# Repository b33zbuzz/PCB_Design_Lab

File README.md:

# PCB_Design_Lab

PCB_Design_Lab is a repository containing resources, designs, and documentation for printed circuit board (PCB) design and experimentation. This repository is intended to provide reference designs, tutorials, and simulation files for students and professionals involved in PCB design projects.

## Features
- Example PCB designs for specific applications.
- Tutorials on PCB design tools and workflows.
- Documentation for each design.

## File Structure
```
PCB_Design_Lab/
├── first/
│   ├── first-backups/            # Backup files for the project
│   │   ├── first-2024-04-02_143817.zip   # Backup from 2024-04-02
│   │   ├── first-2024-04-02_145749.zip   # Backup from 2024-04-02
│   │   ├── first-2024-04-03_172012.zip   # Backup from 2024-04-03
│   │   ├── first-2024-04-09_163603.zip   # Backup from 2024-04-09
│   │   ├── first-2024-04-09_164715.zip   # Backup from 2024-04-09
│   │   ├── first-2024-04-09_170915.zip   # Backup from 2024-04-09
│   │   ├── first-2024-04-09_174335.zip   # Backup from 2024-04-09
│   │   ├── first-2024-04-09_175404.zip   # Backup from 2024-04-09
│   │   ├── first-2024-04-15_153141.zip   # Backup from 2024-04-15
│   │   ├── first-2024-04-15_154005.zip   # Backup from 2024-04-15
│   │   ├── first-2024-04-16_141746.zip   # Backup from 2024-04-16
│   │   ├── first-2024-04-20_152721.zip   # Backup from 2024-04-20
│   │   ├── first-2024-04-20_153831.zip   # Backup from 2024-04-20
│   │   ├── first-2024-04-20_154842.zip   # Backup from 2024-04-20
│   │   ├── first-2024-04-20_155845.zip   # Backup from 2024-04-20
│   │   ├── first-2024-04-20_161707.zip   # Backup from 2024-04-20
│   │   ├── first-2024-04-21_213943.zip   # Backup from 2024-04-21
│   │   ├── first-2024-04-21_214944.zip   # Backup from 2024-04-21
│   │   ├── first-2024-04-21_223350.zip   # Backup from 2024-04-21
│   │   ├── first-2024-04-21_224453.zip   # Backup from 2024-04-21
│   │   ├── first-2024-04-21_233836.zip   # Backup from 2024-04-21
│   │   ├── first-2024-04-22_051006.zip   # Backup from 2024-04-22
│   │   └── first-2024-05-25_000738.zip   # Backup from 2024-05-25
│   ├── a.kicad_sch               # Schematic backup A
│   ├── b.kicad_sch               # Schematic backup B
│   ├── first.kicad_pcb           # PCB layout file for the project
│   ├── first.kicad_prl           # Project layout settings
│   ├── first.kicad_pro           # KiCad project file
│   ├── first.kicad_sch           # Main schematic file
│   ├── fp-info-cache             # Footprint cache file
│   ├── power.kicad_sch           # Power circuit schematic
├── Lab_Report.pdf                # Lab report for the project
├── co-527-manual.pdf             # Manual for CO-527 component
└── README.md                     # Project documentation
```

## Explanation of PDFs
### Lab_Report.pdf
This document provides an in-depth lab report on the PCB design process. It covers the complete workflow, including:
- **General Design Flow**: Steps from request and specification to testing and delivery.
- **Circuit Development**: Breakdown of power, digital, and analog components.
- **KiCad Implementation**: Creating schematics, choosing components, and PCB routing.
- **Design Principles**: Emphasizes key concepts like Ohm's Law, Kirchhoff's Law, and transmission line theory.
- **Conclusion**: Summarizes the learnings and challenges of the PCB design process.

### Lab_Manual.pdf
A comprehensive manual for the CO-527 component, including:
- Specifications and features of the CO-527 component.
- Guidelines for its integration and usage in PCB design.
- Example use cases and performance benchmarks.

## File Formats
- **`.kicad_sch`**: Schematic files containing circuit diagrams for PCB designs in KiCad.
- **`.kicad_pcb`**: PCB layout files used in KiCad PCB design software.
- **`.kicad_pro`**: KiCad project files that organize all design files into a single project.
- **`fp-info-cache`**: Cache file containing footprint data for the project.
- **`.pdf`**: Portable Document Format files for lab reports and manuals.
- **`.zip`**: Archived backups of project files for versioning and recovery.

## Usage
1. Open the KiCad project file (`.kicad_pro`) to access the schematic and PCB layout.
2. Use the `.pdf` files for reference and additional documentation.
3. Explore the backup folder for alternative or previous versions of the schematic.

## Acknowledgments
This repository is the result of the PCB design course at Constructor University Bremen.

---

For questions or feedback, please open an issue in the repository or contact us directly.

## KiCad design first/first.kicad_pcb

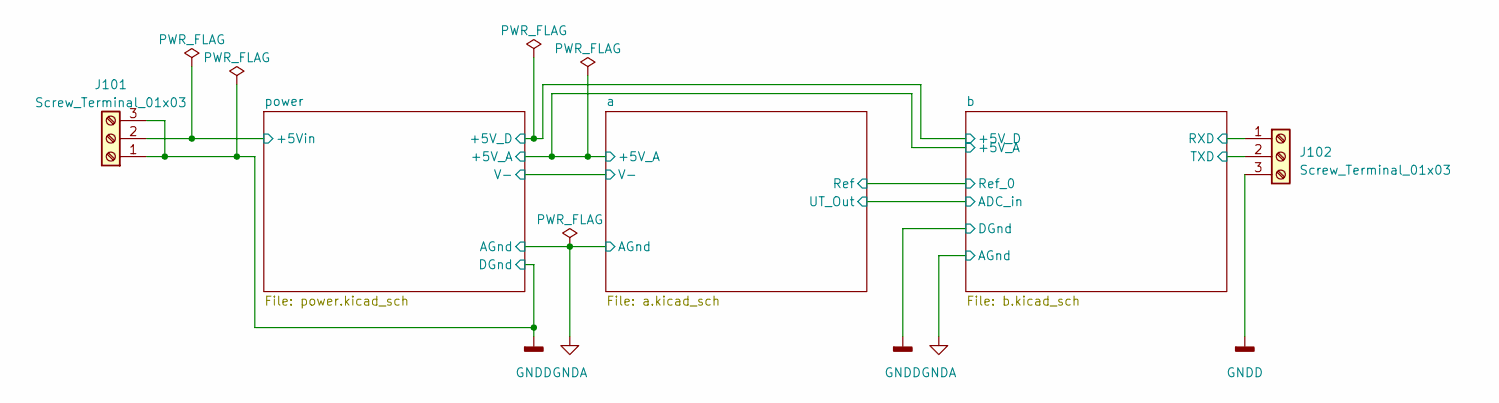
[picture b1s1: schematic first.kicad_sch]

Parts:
J101, J102: Screw_Terminal_01x03; TerminalBlock_Phoenix_MPT-0,5-3-2.54_1x03_P2.54mm_Horizontal

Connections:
/b/RXD: J102.1; also elsewhere on the board
/b/TXD: J102.2; also elsewhere on the board
/power/+5Vin: J101.2; also elsewhere on the board
GNDD: J101.1, J101.3, J102.3; also elsewhere on the board

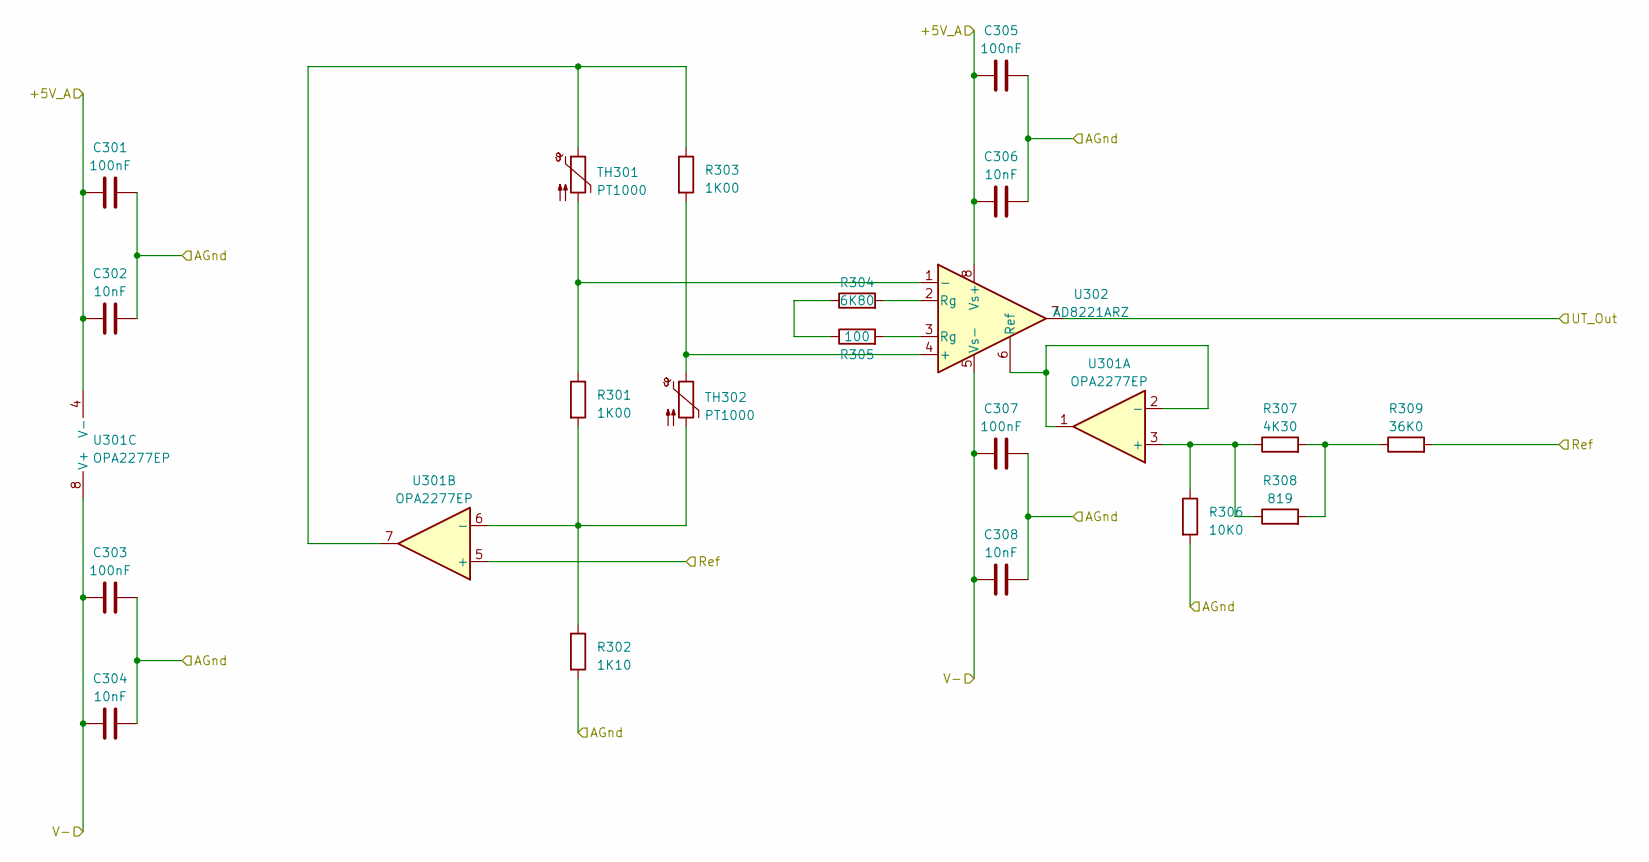
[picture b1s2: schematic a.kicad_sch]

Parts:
C301, C303, C305, C307: 100nF; C_0805_2012Metric
C302, C304, C306, C308: 10nF; C_0805_2012Metric
R301, R303: 1K00; R_0805_2012Metric
R302: 1K10; R_0805_2012Metric
R304: 6K80; R_0805_2012Metric
R305: 100; R_0805_2012Metric
R306: 10K0; R_0805_2012Metric
R307: 4K30; R_0805_2012Metric
R308: 819; R_0805_2012Metric
R309: 36K0; R_0805_2012Metric
TH301, TH302: PT1000; R_0805_2012Metric
U301: OPA2277EP; SOIC-8_3.9x4.9mm_P1.27mm
U302: AD8221ARZ; SOIC-8_3.9x4.9mm_P1.27mm

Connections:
/a/+5V_A: C301.1, C302.1, C305.1, C306.1, U301.4 (V-), U302.8 (Vs+); also elsewhere on the board
/a/Ref: R309.2, U301.5 (+); also elsewhere on the board
/a/UT_Out: U302.7; also elsewhere on the board
/a/V-: C303.1, C304.1, C307.1, C308.1, U301.8 (V+), U302.5 (Vs-); also elsewhere on the board
GNDA: C301.2, C302.2, C303.2, C304.2, C305.2, C306.2, C307.2, C308.2, R302.2, R306.2; also elsewhere on the board
unnamed: R303.1, TH301.1, U301.7
unnamed: R304.1, R305.1
unnamed: R304.2, U302.2 (Rg)
unnamed: R305.2, U302.3 (Rg)
unnamed: R307.2, R308.2, R309.1
unnamed: R306.1, R307.1, R308.1, U301.3 (+)
unnamed: U301.1, U301.2 (-), U302.6 (Ref)
unnamed: R301.2, R302.1, TH302.2, U301.6 (-)
unnamed: R303.2, TH302.1, U302.4 (+)
unnamed: R301.1, TH301.2, U302.1 (-)

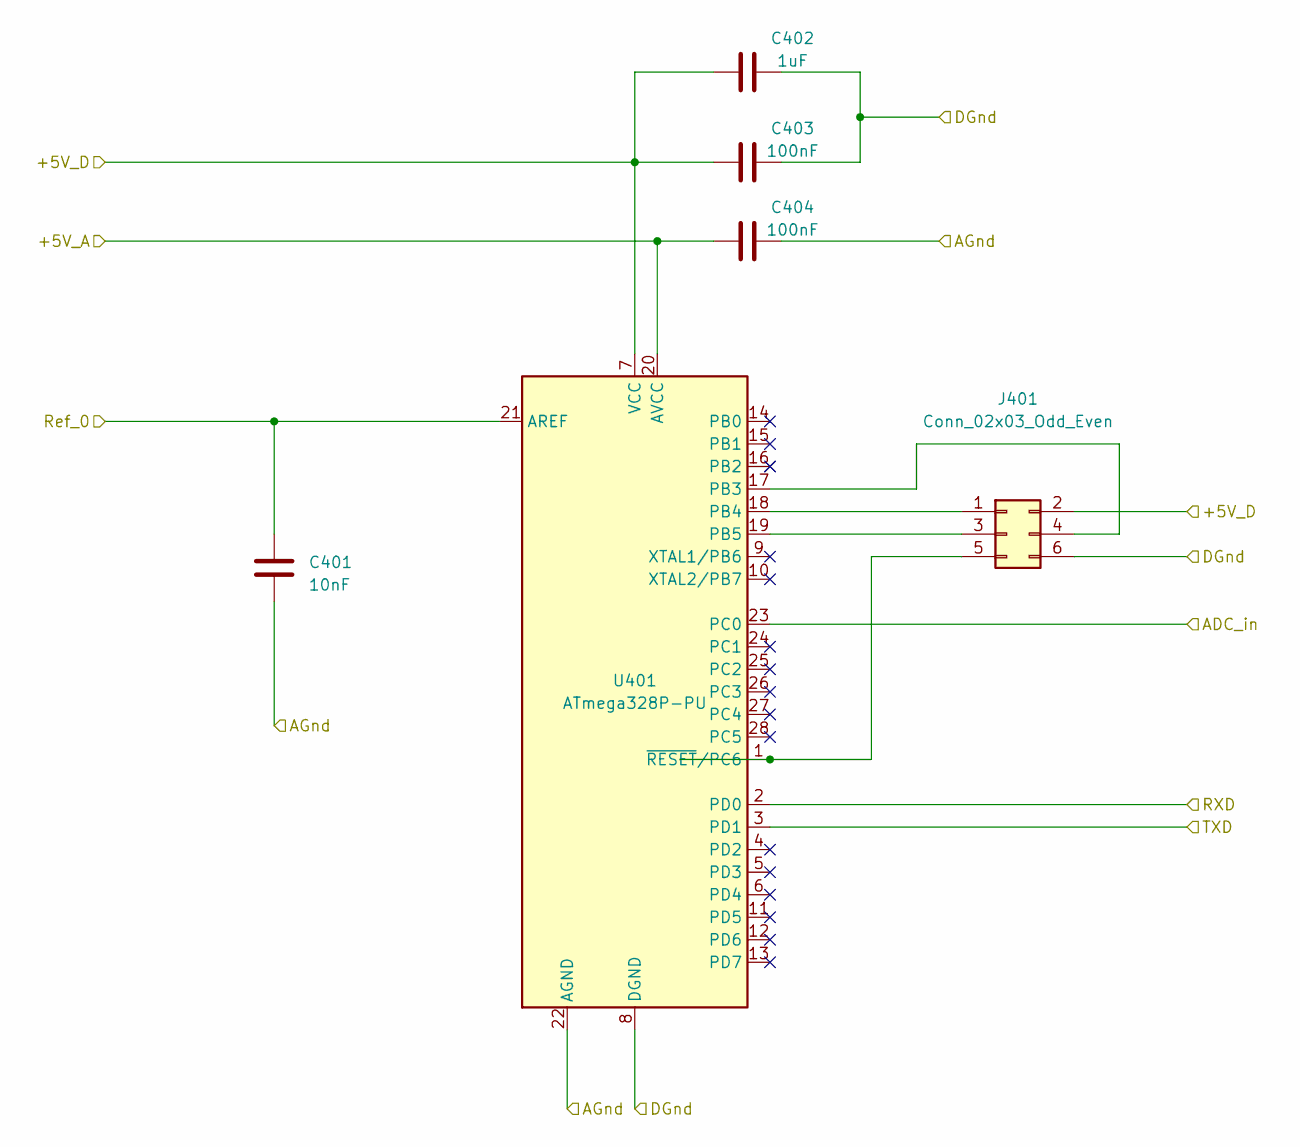
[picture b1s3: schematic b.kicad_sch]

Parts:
C401: 10nF; C_0805_2012Metric
C402: 1uF; C_0805_2012Metric
C403, C404: 100nF; C_0805_2012Metric
J401: Conn_02x03_Odd_Even; PinHeader_2x03_P2.54mm_Vertical
U401: ATmega328P-PU; DIP-28_W7.62mm

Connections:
/a/+5V_A: C404.1, U401.20 (AVCC); also elsewhere on the board
/a/Ref: C401.2, U401.21 (AREF); also elsewhere on the board
/a/UT_Out: U401.23 (PC0); also elsewhere on the board
/b/+5V_D: C402.1, C403.1, J401.2, U401.7 (VCC); also elsewhere on the board
/b/RXD: U401.2 (PD0); also elsewhere on the board
/b/TXD: U401.3 (PD1); also elsewhere on the board
GNDA: C401.1, C404.2, U401.22 (AGND); also elsewhere on the board
GNDD: C402.2, C403.2, J401.6, U401.8 (DGND); also elsewhere on the board
unnamed: J401.1, U401.18 (PB4)
unnamed: J401.3, U401.19 (PB5)
unnamed: J401.4, U401.17 (PB3)
unnamed: J401.5, U401.1 (~RESET/PC6)

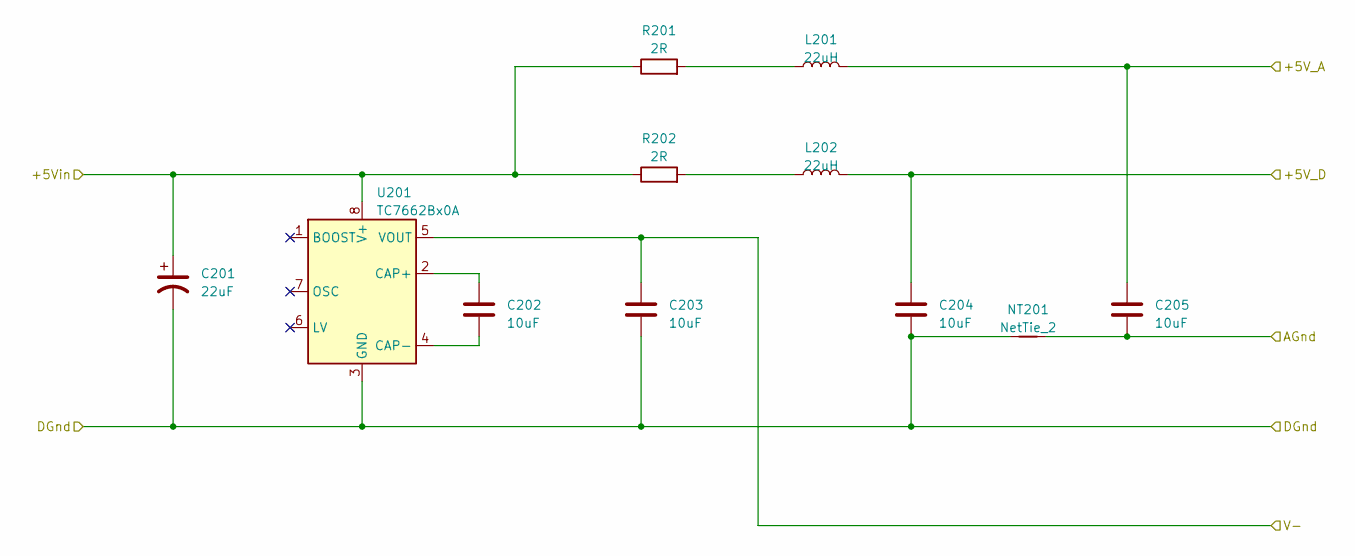
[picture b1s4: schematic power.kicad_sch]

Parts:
C201: 22uF; CP_EIA-7343-15_Kemet-W
C202, C203, C204, C205: 10uF; C_0805_2012Metric
L201, L202: 22uH; L_1210_3225Metric
NT201: NetTie_2; NetTie-2_SMD_Pad0.5mm
R201, R202: 2R; R_0805_2012Metric
U201: TC7662Bx0A; SOIC-8_3.9x4.9mm_P1.27mm

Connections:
/a/+5V_A: C205.1, L201.2; also elsewhere on the board
/a/V-: C203.1, U201.5 (VOUT); also elsewhere on the board
/b/+5V_D: C204.1, L202.2; also elsewhere on the board
/power/+5Vin: C201.1, R201.1, R202.1, U201.8 (V+); also elsewhere on the board
GNDA: C205.2, NT201.2; also elsewhere on the board
GNDD: C201.2, C203.2, C204.2, NT201.1, U201.3 (GND); also elsewhere on the board
unnamed: L201.1, R201.2
unnamed: L202.1, R202.2
unnamed: C202.1, U201.2 (CAP+)
unnamed: C202.2, U201.4 (CAP-)

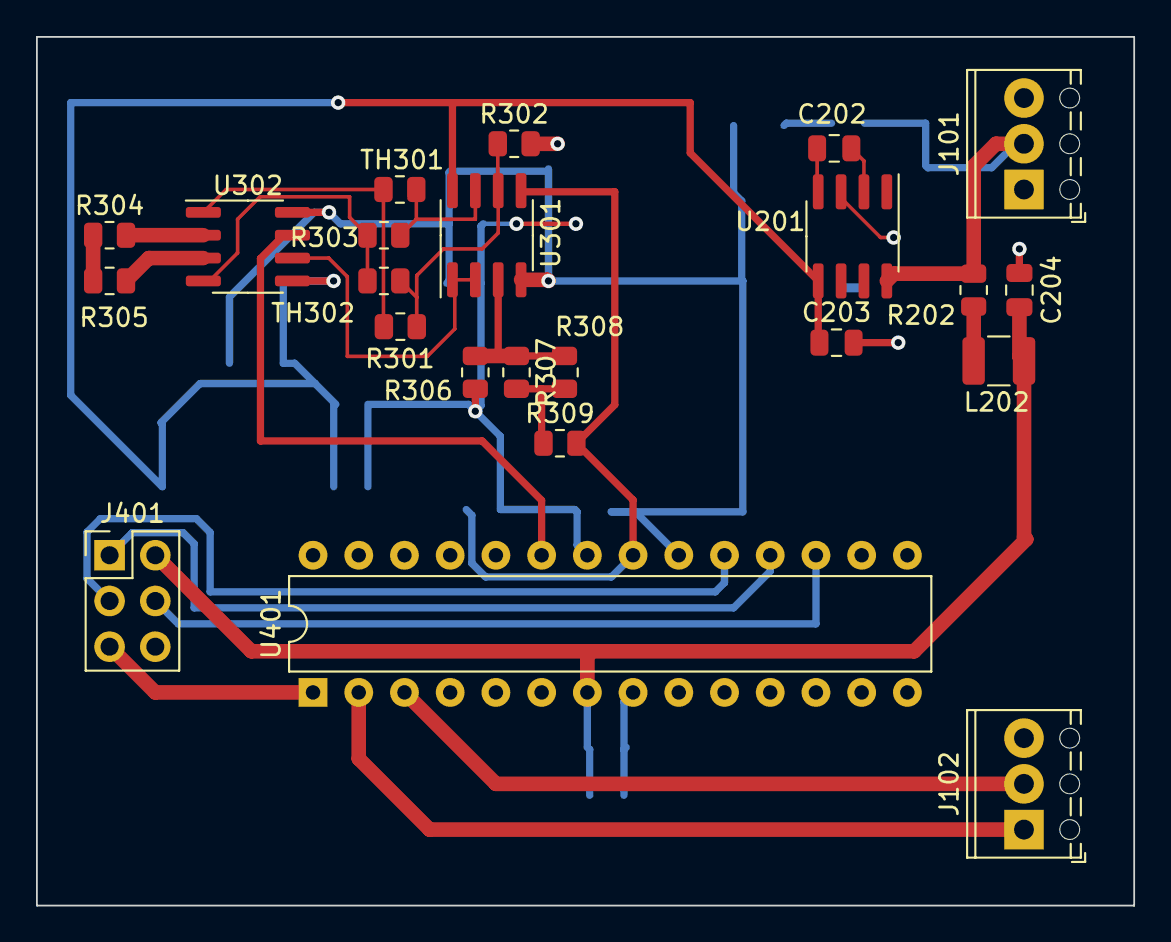
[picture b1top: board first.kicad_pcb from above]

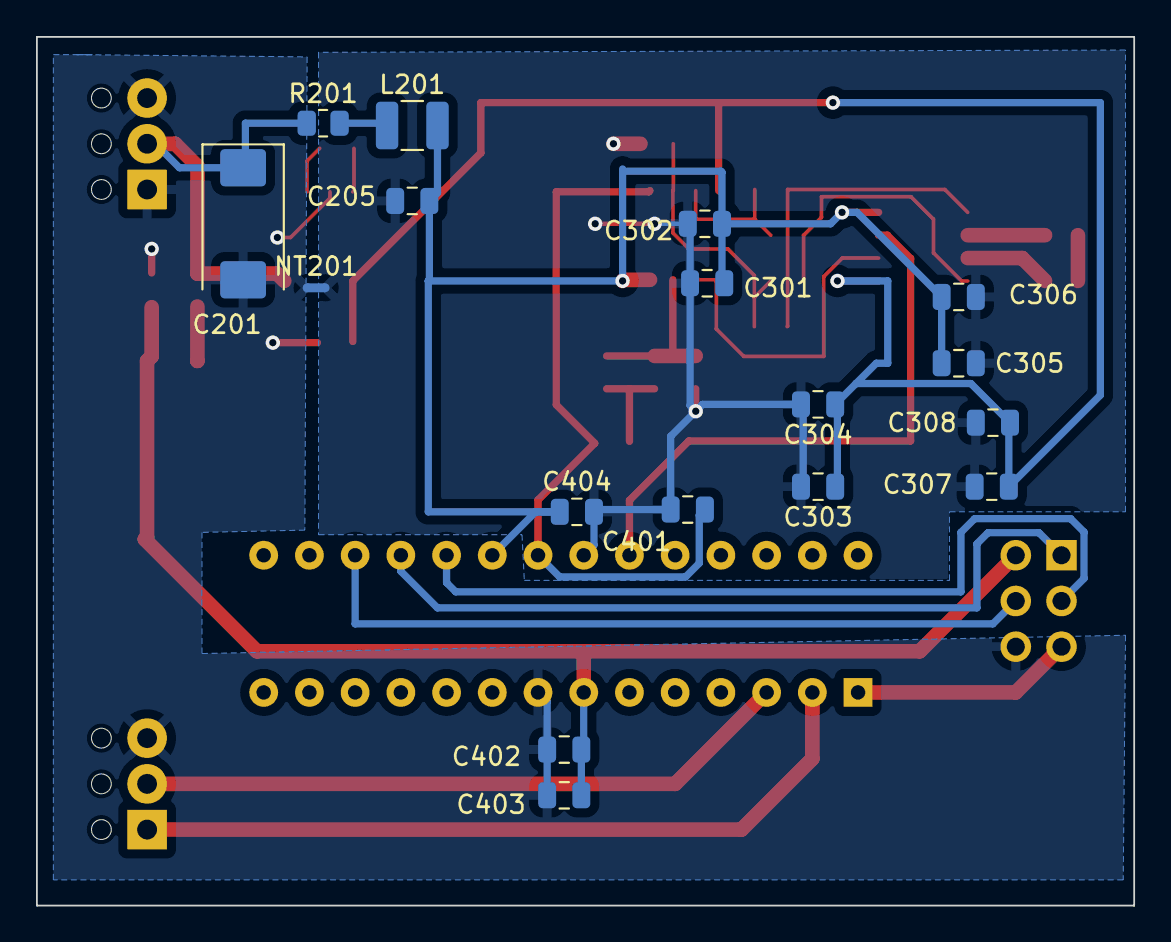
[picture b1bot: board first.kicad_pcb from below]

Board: 2 copper layers, 61.0 x 48.3 mm, 40 parts (17 on the bottom side), 28 nets.

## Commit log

2025-01-05 added contents
2025-01-05 changed filename
